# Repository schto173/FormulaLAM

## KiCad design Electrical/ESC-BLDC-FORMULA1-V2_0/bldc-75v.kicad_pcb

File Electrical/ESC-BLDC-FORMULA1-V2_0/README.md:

# ESC-BLDC-FORMULA1 V2.0 (work in progress – placement only, NOT routed, NOT orderable)

Redesign of the V1.2 ESC HAT (DRV8353RS + 6x CSD19532Q5B, SimpleFOC, NUCLEO-G474RE). V1.2 stays untouched in
`../ESC-BLDC-FORMULA1-V1_2/` (those are the files that were ordered).

## Background: how V1.2 board #1 failed
At ~45 V and ~93 % modulation the DRV8353 faulted and its internal low-side gate-drive supply was permanently
damaged (GDUV, VGLS 3 V instead of ~11 V). Not a component defect (C29 is not the cause); the root cause is not
determined yet – see `../ESC-BLDC-FORMULA1-V1_2/CLAUDE.md`. Trace length alone does not explain it: TI's
DRV8353RH-EVM has gate paths of the same length as V1.2. V2 follows that TI board (same parts, low-side shunts
into the DRV8353 amplifiers, DRV beside the FETs) and must survive a 60 V battery.

## What changed vs V1.2
- **Power supply (option A):** DRV8353 buck makes 12 V (VBUCK) for VM only, faster (R34 180k ≈ 480 kHz, L1 100 µH 6x6);
  TPS562201 makes 5 V from 12 V (replaces the LM5164 58 V buck). 5 V now comes up at ~6 V bus.
- **Phase voltage sensing removed** (U3 + dividers) – SimpleFOC does not use it. Fuse F1 removed (fuse goes in the battery cable).
- **Bus caps:** 3x THT 330 µF 100 V, 16x25 mm (C11, C21, C68; Samyoung NXA C346987 as on V1.2, 1.65 A ripple each
  = ~5 A, enough for 20 A bursts) + MLCCs in every half-bridge; TVS SMCJ60A (C224057; starts conducting at 66.7 V, so the board is safe with up to a 60 V battery).
- **Wheel speed input** J11 (JST-XH 3P: 1 = +5V, 2 = SIG, 3 = GND) → D10 / R78 4.7k to 3V3 / C73 → **PC6 (TIM3_CH1)**.
- **Test points:** TP1/TP2 Keystone 5001 GND loops for the scope clip (power side / logic side), pads TP3 VGLS,
  TP4 VCP, TP5 12 V, TP6 5 V, TP7 3.3 V.
- **Motor pads** are three single 2.5 mm² solder-wire pads: J6 = MOTC, J12 = MOTB, J13 = MOTA.
- Freed Nucleo pins: PB0, PC0, PC2 (were phase voltage sensing).

## Layout (board 110.5 x 90 mm, x 143–253.5 / y 44–134)
- Sits on top of the Nucleo (sockets on our bottom side); the **ST-LINK / USB end of the Nucleo stays uncovered**.
- **Power stage "pinwheel"** (after TI's DRV8353RS EVM): DRV rotated 45°, one half-bridge cell per DRV pin group –
  phase C above, B right, A below – so every phase gets a short gate/sense path (14–26 mm straight line; V1 had
  30–45 mm). Each cell: shunt (Kelvin, net tie under the body) → LS FET over HS FET → motor pad at the outer edge,
  MLCCs right beside the HS drain. Route GHx with SHx and GLx with SPx as tight pairs.
- Battery pads J5 + TVS at the top-right edge, bulk caps in the right corners; plan an inner VDRAIN plane under
  the power stage and a solid GND plane.
- Connectors next to the Nucleo pins they use: wheel / CAN / halls in the strip above CN10, UART / LEDs / throttle
  in the strip below CN7.
- M3 holes in the 4 corners; the Nucleo's own 3 holes are kept for standoffs.

## Before ordering
- Route the board; check that the HAT clears the Nucleo's Arduino headers (socket height).
- `tools/lcsc_map.py` is still the V1.2 map → update for V2 parts (U6, L3, C68–C73, R75–R78, D10, J11, J12, J13,
  TP1/TP2 = C238122; TP3–TP7 are bare pads) before running `gen_jlc.py`.
- Firmware: wheel input on PC6; 5 V rail now from VBUCK.

Placement is scripted: `tools/v2_place.py` (positions), `tools/v2_pcb_prepare.py` (netlist → board),
`tools/v2_sch_*.py` (schematic changes, each run once).

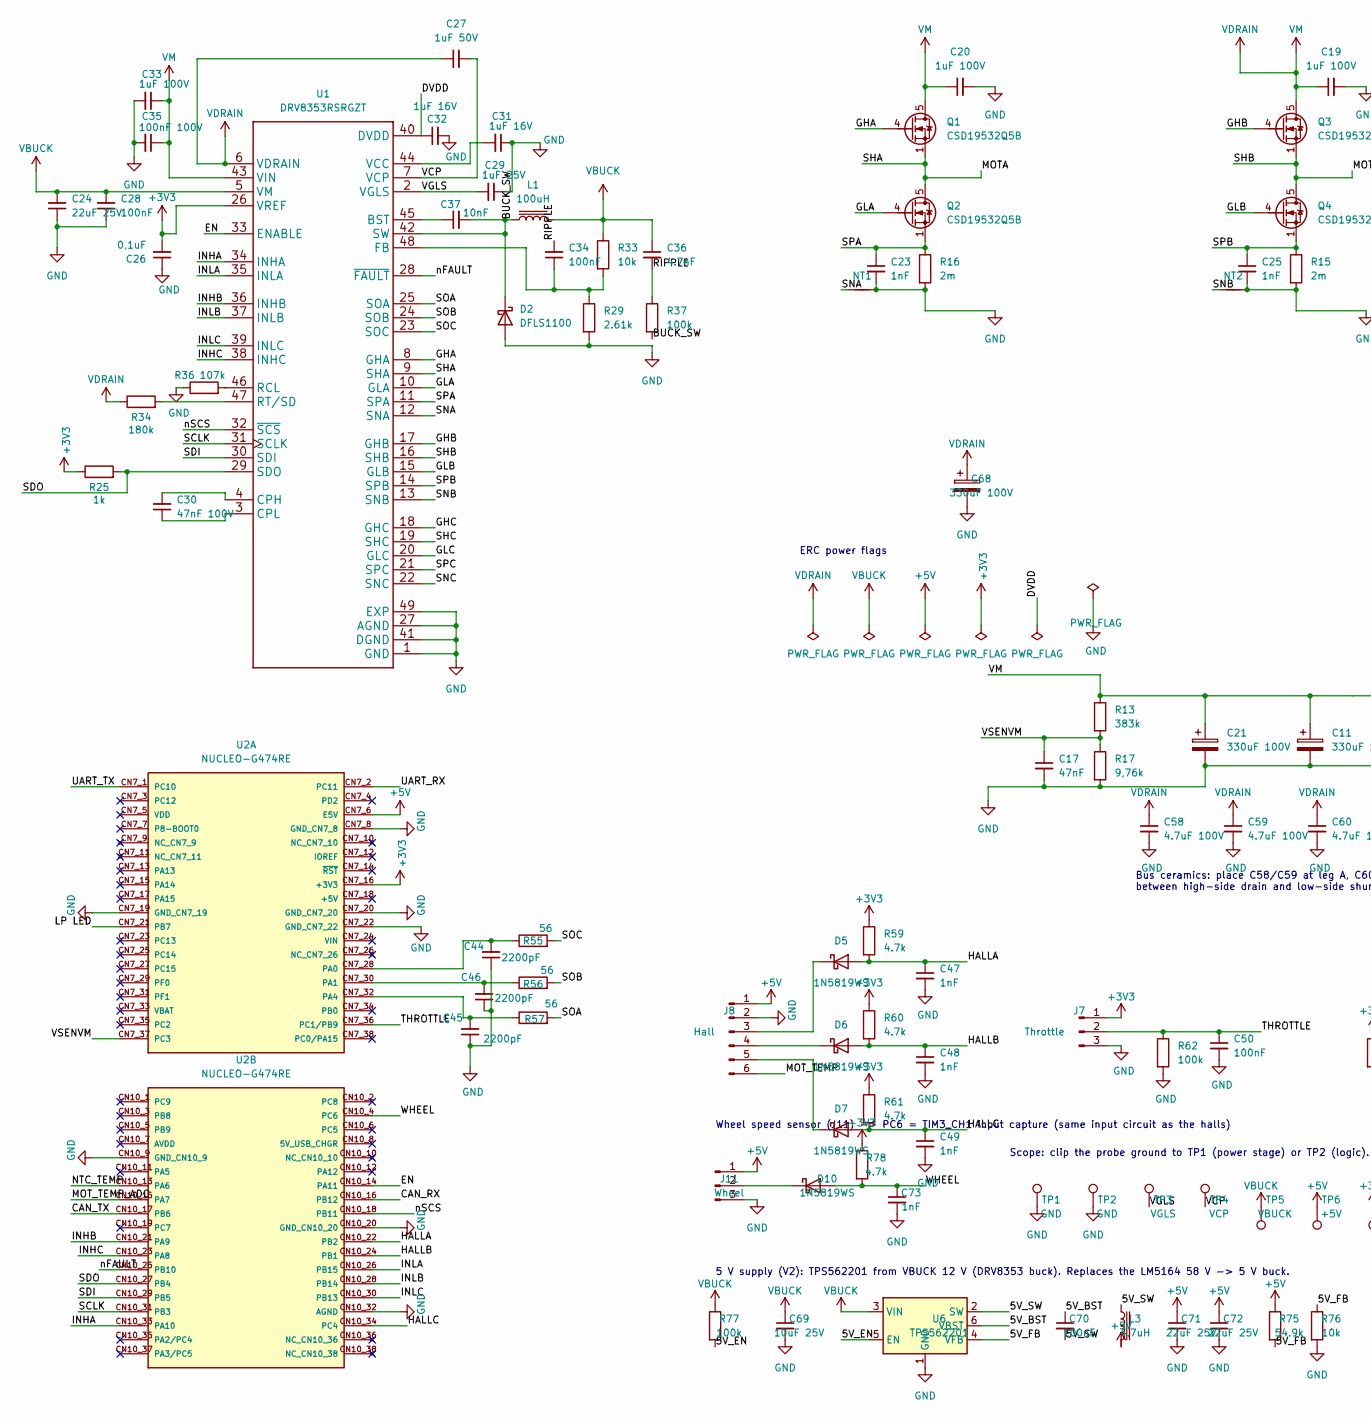
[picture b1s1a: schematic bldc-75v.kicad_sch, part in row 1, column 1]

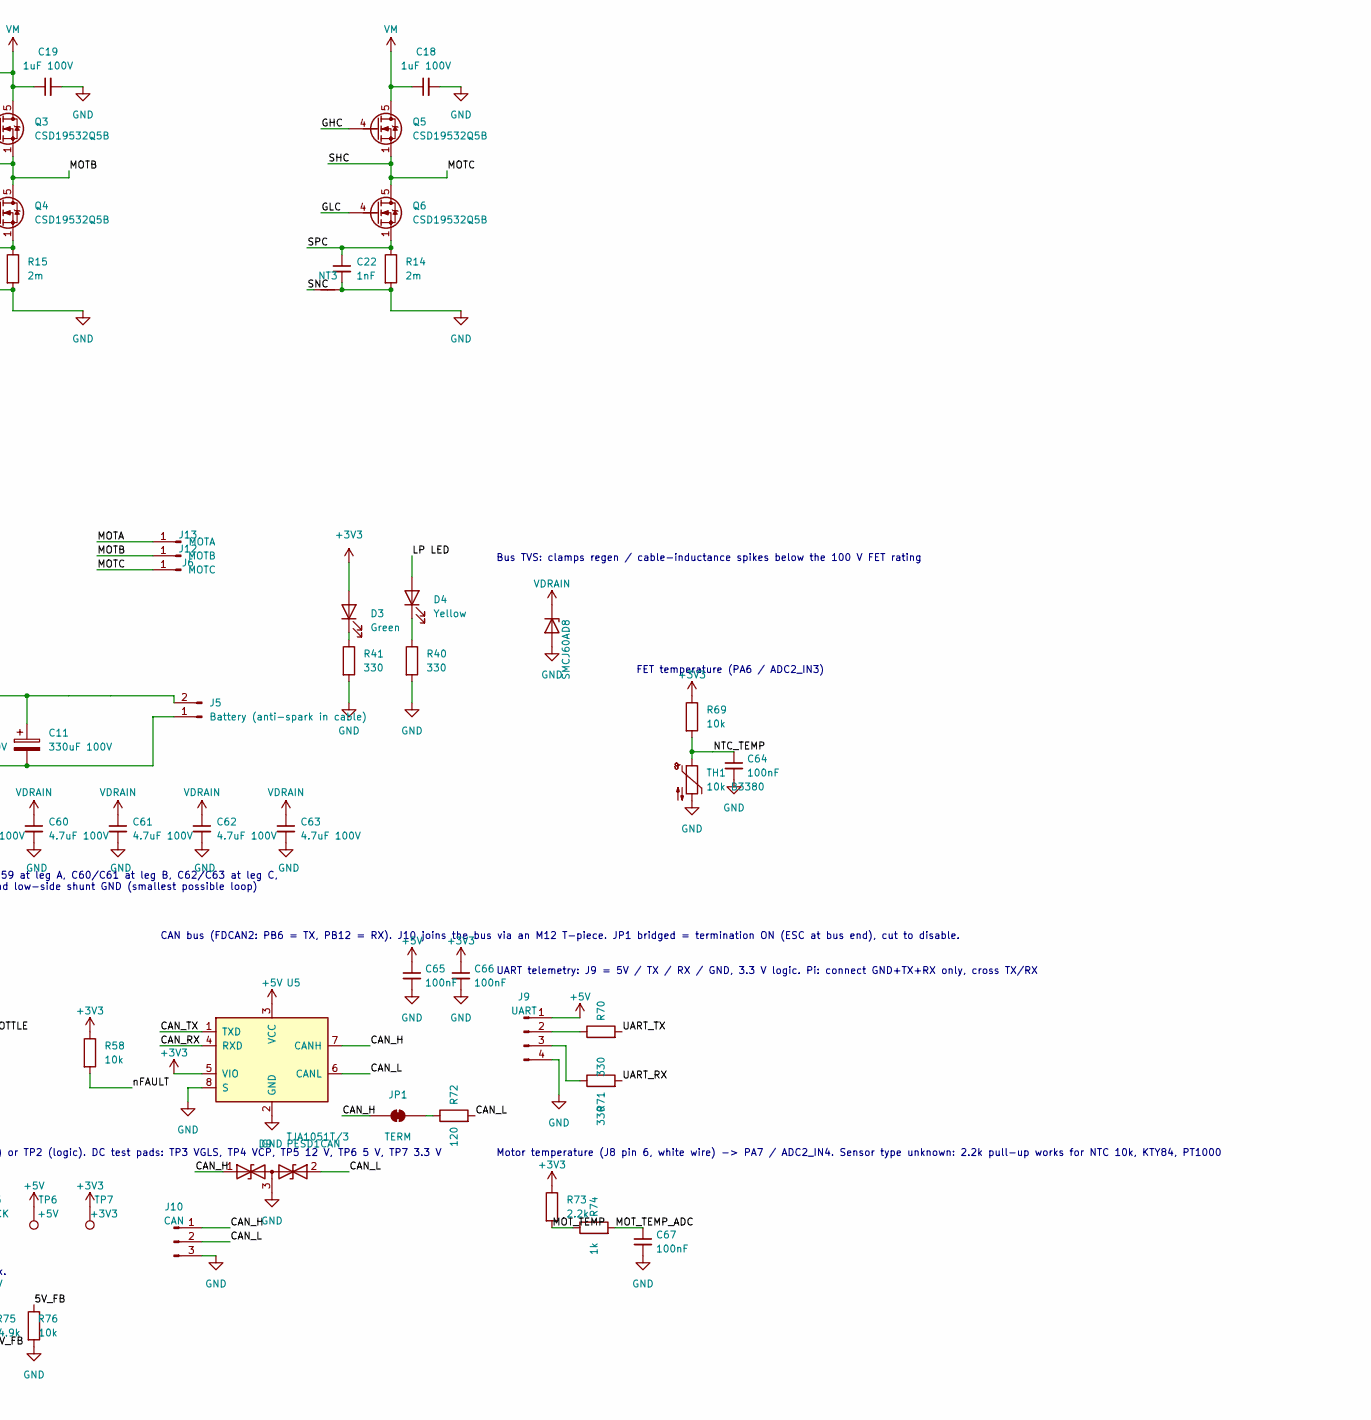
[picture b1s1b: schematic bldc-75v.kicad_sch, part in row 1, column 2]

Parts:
C11, C21, C68: 330uF 100V; CP_Radial_D16.0mm_P7.50mm; LCSC C346987
C17: 47nF; C_0603_1608Metric; LCSC C1622
C18, C19, C20, C33: 1uF 100V; C_1206_3216Metric; LCSC C13832
C22, C23, C25, C47, C48, C49, C73: 1nF; C_0603_1608Metric; LCSC C1588
C24: 22uF 25V; C_0805_2012Metric; LCSC C45783
C26: 0,1uF; C_0603_1608Metric; LCSC C14663
C27: 1uF 50V; C_0603_1608Metric; LCSC C15849
C28, C34, C50, C64, C65, C66, C67, C70: 100nF; C_0603_1608Metric; LCSC C14663
C29: 1uF 25V; C_0603_1608Metric; LCSC C15849
C30: 47nF 100V; C_0603_1608Metric; LCSC C576852
C31, C32: 1uF 16V; C_0603_1608Metric; LCSC C15849
C35: 100nF 100V; C_0805_2012Metric; LCSC C28233
C36: 4.7nF; C_0603_1608Metric; LCSC C53987
C37: 10nF; C_0603_1608Metric; LCSC C57112
C44, C45, C46: 2200pF; C_0603_1608Metric; LCSC C1604
C58, C59, C60, C61, C62, C63: 4.7uF 100V; C_1210_3225Metric; LCSC C385986
C69: 10uF 25V; C_0805_2012Metric; LCSC C15850
C71, C72: 22uF 25V; C_1206_3216Metric; LCSC C12891
D2: DFLS1100; D_PowerDI-123; LCSC C107674
D3: Green; LED_0603_1608Metric; LCSC C12624
D4: Yellow; LED_0603_1608Metric; LCSC C2287
D5, D6, D7, D10: 1N5819WS; D_SOD-323; LCSC C191023
D8: SMCJ60A; D_SMC; LCSC C224057
D9: PESD1CAN; SOT-23; LCSC C15771
J5: Battery (anti-spark in cable); SolderWire-2.5sqmm_1x02_P8.8mm_D2.4mm_OD4.4mm
J6: MOTC; SolderWire-2.5sqmm_1x01_D2.4mm_OD4.4mm
J7: Throttle; JST_XH_B3B-XH-A_1x03_P2.50mm_Vertical; LCSC C144394
J8: Hall; JST_XH_B6B-XH-A_1x06_P2.50mm_Vertical; LCSC C144397
J9: UART; JST_XH_B4B-XH-A_1x04_P2.50mm_Vertical; LCSC C144395
J10: CAN; JST_XH_B3B-XH-A_1x03_P2.50mm_Vertical; LCSC C144394
J11: Wheel; JST_XH_B3B-XH-A_1x03_P2.50mm_Vertical; LCSC C144394
J12: MOTB; SolderWire-2.5sqmm_1x01_D2.4mm_OD4.4mm
J13: MOTA; SolderWire-2.5sqmm_1x01_D2.4mm_OD4.4mm
JP1: TERM; SolderJumper-2_P1.3mm_Bridged_RoundedPad1.0x1.5mm
L1: 100uH; L_Sunlord_SWPA6045S; LCSC C60633
L3: 4.7uH; L_Sunlord_SWPA4030S; LCSC C57269
NT1, NT2, NT3: NetTie_2; NetTie-2_SMD_Pad0.5mm
Q1, Q2, Q3, Q4, Q5, Q6: CSD19532Q5B; TDSON-8-1; LCSC C473333
R13: 383k; R_1206_3216Metric; LCSC C247277
R14, R15, R16: 2m; R_2512_6332Metric; LCSC C154685
R17: 9,76k; R_0603_1608Metric; LCSC C23128
R25, R74: 1k; R_0603_1608Metric; LCSC C21190
R29: 2.61k; R_0603_1608Metric; LCSC C22942
R33, R58, R69, R76: 10k; R_0603_1608Metric; LCSC C25804
R34: 180k; R_1206_3216Metric; LCSC C17923
R36: 107k; R_0603_1608Metric; LCSC C14889
R37: 100k; R_1206_3216Metric; LCSC C17900
R40, R41, R70, R71: 330; R_0603_1608Metric; LCSC C23138
R55, R56, R57: 56; R_0603_1608Metric; LCSC C25196
R59, R60, R61, R78: 4.7k; R_0603_1608Metric; LCSC C23162
R62, R77: 100k; R_0603_1608Metric; LCSC C25803
R72: 120; R_0603_1608Metric; LCSC C22787
R73: 2.2k; R_0603_1608Metric; LCSC C4190
R75: 54.9k; R_0603_1608Metric; LCSC C23077
TH1: 10k B3380; R_0402_1005Metric; LCSC C77131
TP1, TP2: GND; TestPoint_Keystone_5000-5004_Miniature; LCSC C238122
TP3: VGLS; TestPoint_Pad_D1.5mm
TP4: VCP; TestPoint_Pad_D1.5mm
TP5: VBUCK; TestPoint_Pad_D1.5mm
TP6: +5V; TestPoint_Pad_D1.5mm
TP7: +3V3; TestPoint_Pad_D1.5mm
U1: DRV8353RSRGZT; QFN50P700X700X100-49N; PARTREV A; LCSC C506246
U2: NUCLEO-G474RE; Nucleo64_Morpho_HAT; PARTREV 17
U5: TJA1051T/3; SOIC-8_3.9x4.9mm_P1.27mm; LCSC C38695
U6: TPS562201; TSOT-23-6; LCSC C90061

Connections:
+3V3: C26.2, C66.1, D3.2 (A), J7.1, R25.1, R58.1, R59.1, R60.1, R61.1, R69.1, R73.1, R78.1, TP7.1, U1.26 (VREF), U2.CN7_16 (+3V3), U5.5 (VIO)
+5V: C65.1, C71.1, C72.1, J8.1, J9.1, J11.1, L3.2, R75.1, TP6.1, U2.CN7_6 (E5V), U5.3 (VCC)
/5V_BST: C70.1, U6.6 (VBST)
/5V_EN: R77.2, U6.5 (EN)
/5V_FB: R75.2, R76.1, U6.4 (VFB)
/5V_SW: C70.2, L3.1, U6.2 (SW)
/BUCK_SW: C37.2, D2.1 (K), L1.1, R37.2, U1.42 (SW)
/CAN_H: D9.1 (A1), J10.1, JP1.1 (A), U5.7 (CANH)
/CAN_L: D9.2 (A2), J10.2, R72.2, U5.6 (CANL)
/CAN_RX: U2.CN10_16 (PB12), U5.4 (RXD)
/CAN_TX: U2.CN10_17 (PB6), U5.1 (TXD)
/DVDD: C32.1, U1.40 (DVDD)
/EN: U1.33 (ENABLE), U2.CN10_14 (PA11)
/GHA: Q1.4 (G), U1.8 (GHA)
/GHB: Q3.4 (G), U1.17 (GHB)
/GHC: Q5.4 (G), U1.18 (GHC)
/GLA: Q2.4 (G), U1.10 (GLA)
/GLB: Q4.4 (G), U1.15 (GLB)
/GLC: Q6.4 (G), U1.20 (GLC)
/HALLA: C47.1, D5.2 (A), R59.2, U2.CN10_22 (PB2)
/HALLB: C48.1, D6.2 (A), R60.2, U2.CN10_24 (PB1)
/HALLC: C49.1, D7.2 (A), R61.2, U2.CN10_34 (PC4)
/INHA: U1.34 (INHA), U2.CN10_33 (PA10)
/INHB: U1.36 (INHB), U2.CN10_21 (PA9)
/INHC: U1.38 (INHC), U2.CN10_23 (PA8)
/INLA: U1.35 (INLA), U2.CN10_26 (PB15)
/INLB: U1.37 (INLB), U2.CN10_28 (PB14)
/INLC: U1.39 (INLC), U2.CN10_30 (PB13)
/LP LED: D4.2 (A), U2.CN7_21 (PB7)
/MOTA: J13.1, Q1.1 (S), Q1.2 (S), Q1.3 (S), Q2.5 (D), U1.9 (SHA)
/MOTB: J12.1, Q3.1 (S), Q3.2 (S), Q3.3 (S), Q4.5 (D), U1.16 (SHB)
/MOTC: J6.1, Q5.1 (S), Q5.2 (S), Q5.3 (S), Q6.5 (D), U1.19 (SHC)
/MOT_TEMP: J8.6, R73.2, R74.1
/MOT_TEMP_ADC: C67.1, R74.2, U2.CN10_15 (PA7)
/NTC_TEMP: C64.1, R69.2, TH1.1, U2.CN10_13 (PA6)
/RIPPLE: C34.2, C36.2, R37.1
/SCLK: U1.31 (SCLK), U2.CN10_31 (PB3)
/SDI: U1.30 (SDI), U2.CN10_29 (PB5)
/SDO: R25.2, U1.29 (SDO), U2.CN10_27 (PB4)
/SNA: NT1.1, U1.12 (SNA)
/SNB: NT2.1, U1.13 (SNB)
/SNC: NT3.1, U1.22 (SNC)
/SOA: R57.2, U1.25 (SOA)
/SOB: R56.2, U1.24 (SOB)
/SOC: R55.2, U1.23 (SOC)
/SPA: C23.1, Q2.1 (S), Q2.2 (S), Q2.3 (S), R16.1, U1.11 (SPA)
/SPB: C25.1, Q4.1 (S), Q4.2 (S), Q4.3 (S), R15.1, U1.14 (SPB)
/SPC: C22.1, Q6.1 (S), Q6.2 (S), Q6.3 (S), R14.1, U1.21 (SPC)
/THROTTLE: C50.1, J7.2, R62.1, U2.CN7_36 (PC1/PB9)
/UART_RX: R71.2, U2.CN7_2 (PC11)
/UART_TX: R70.2, U2.CN7_1 (PC10)
/VCP: C27.2, TP4.1, U1.7 (VCP)
/VGLS: C29.2, TP3.1, U1.2 (VGLS)
/VSENVM: C17.1, R13.2, R17.1, U2.CN7_37 (PC3)
/WHEEL: C73.1, D10.2 (A), R78.2, U2.CN10_4 (PC6)
/nFAULT: R58.2, U1.28 (~FAULT), U2.CN10_25 (PB10)
/nSCS: U1.32 (~SCS), U2.CN10_18 (PB11)
GND: C11.2, C17.2, C18.2, C19.2, C20.2, C21.2, C22.2, C23.2, C24.1, C25.2, C26.1, C28.1, C29.1, C31.1, C32.2, C33.2, C35.2, C44.1, C45.1, C46.1, C47.2, C48.2, C49.2, C50.2, C58.2, C59.2, C60.2, C61.2, C62.2, C63.2, C64.2, C65.2, C66.2, C67.2, C68.2, C69.2, C71.2, C72.2, C73.2, D2.2 (A), D8.2 (A), D9.3 (common), J5.1, J7.3, J8.2, J9.4, J10.3, J11.3, NT1.2, NT2.2, NT3.2, R14.2, R15.2, R16.2, R17.2, R29.2, R36.1, R40.2, R41.2, R62.2, R76.2, TH1.2, TP1.1, TP2.1, U1.1 (GND), U1.27 (AGND), U1.41 (DGND), U1.49 (EXP), U2.CN7_8 (GND_CN7_8), U2.CN7_19 (GND_CN7_19), U2.CN7_20 (GND_CN7_20), U2.CN7_22 (GND_CN7_22), U2.CN10_9 (GND_CN10_9), U2.CN10_20 (GND_CN10_20), U2.CN10_32 (AGND), U5.2 (GND), U5.8 (S), U6.1 (GND)
unnamed: D3.1 (K), R41.1
unnamed: D4.1 (K), R40.1
unnamed: D5.1 (K), J8.3
unnamed: D6.1 (K), J8.4
unnamed: D7.1 (K), J8.5
unnamed: D10.1 (K), J11.2
unnamed: J9.2, R70.1
unnamed: J9.3, R71.1
unnamed: JP1.2 (B), R72.1
unnamed: C37.1, U1.45 (BST)
unnamed: C30.2, U1.4 (CPH)
unnamed: C30.1, U1.3 (CPL)
unnamed: C34.1, R29.1, R33.2, U1.48 (FB)
unnamed: R36.2, U1.46 (RCL)
unnamed: R34.2, U1.47 (RT/SD)
unnamed: C31.2, U1.44 (VCC)
unnamed: C44.2, R55.1, U2.CN7_28 (PA0)
unnamed: C46.2, R56.1, U2.CN7_30 (PA1)
unnamed: C45.2, R57.1, U2.CN7_32 (PA4)
VBUCK: C24.2, C28.2, C36.1, C69.1, L1.2, R33.1, R77.1, TP5.1, U1.5 (VM), U6.3 (VIN)
VDRAIN: C11.1, C18.1, C19.1, C20.1, C21.1, C27.1, C33.1, C35.1, C58.1, C59.1, C60.1, C61.1, C62.1, C63.1, C68.1, D8.1 (K), J5.2, Q1.5 (D), Q3.5 (D), Q5.5 (D), R13.1, R34.1, U1.6 (VDRAIN), U1.43 (VIN)

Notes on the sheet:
Bus ceramics: place C58/C59 at leg A, C60/C61 at leg B, C62/C63 at leg C, between high-side drain and low-side shunt GND (smallest possible loop)
ERC power flags
Bus TVS: clamps regen / cable-inductance spikes below the 100 V FET rating
FET temperature (PA6 / ADC2_IN3)
UART telemetry: J9 = 5V / TX / RX / GND, 3.3 V logic. Pi: connect GND+TX+RX only, cross TX/RX
CAN bus (FDCAN2: PB6 = TX, PB12 = RX). J10 joins the bus via an M12 T-piece. JP1 bridged = termination ON (ESC at bus end), cut to disable.
Motor temperature (J8 pin 6, white wire) -> PA7 / ADC2_IN4. Sensor type unknown: 2.2k pull-up works for NTC 10k, KTY84, PT1000
5 V supply (V2): TPS562201 from VBUCK 12 V (DRV8353 buck). Replaces the LM5164 58 V -> 5 V buck.
Wheel speed sensor (J11) -> PC6 = TIM3_CH1 input capture (same input circuit as the halls)
Scope: clip the probe ground to TP1 (power stage) or TP2 (logic). DC test pads: TP3 VGLS, TP4 VCP, TP5 12 V, TP6 5 V, TP7 3.3 V

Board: 4 copper layers, 122 parts (0 on the bottom side), 79 nets, no tracks yet.

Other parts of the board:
H1, H2, H3, H4: M3; MountingHole_3.2mm_M3

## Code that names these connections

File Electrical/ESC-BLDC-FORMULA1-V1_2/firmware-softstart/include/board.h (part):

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// ---- throttle (J7: 1 = 3.3 V, 2 = signal, 3 = GND; 100k pull-down -> unplugged reads 0 V) - step 5 only --
// Throttle 0..100 % -> 0..limit A (limit = CURRENT_LIMIT, change live with "L"). Calibrate live: release fully
// + "AI", press fully + "AF"; then put the printed values here.
#define THROTTLE_ON_AT_START 1    // 1: throttle controls the current after start-up ("A0" = off, T commands again)
// hall throttle on 3.3 V (2026-10-14): ~0.87 V released, ~2.60 V fully pressed -> with dead band:
#define THROTTLE_IDLE_V   0.97f   // V at and below: 0 A
#define THROTTLE_FULL_V   2.55f   // V at and above: full current
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// while the motor is slower than the target; never negative (no braking - the freewheel hub can't pass it on).
// The current rises at most CURRENT_RAMP_A_S (soft freewheel engagement) and drops at once. Released = 0 A,
// the motor spins down, the car rolls; once the motor stands still the DRV goes to COAST (all FETs off).
#define GEAR_RATIO        9.41f   // motor turns per wheel turn (2026-10-29: pinion 15 -> 22 teeth, 13.8 x 15/22; was 8:1, 13.8:1)
#define WHEEL_DIAMETER_M  0.508f  // outer diameter with tyre (20" is often 0.48-0.50) <- CONFIRM
#define SPEED_MAX_KMH     40.0f   // throttle 100 %
#define MOTOR_DIRECTION   1       // +1 / -1: which way is forward (+1 = normal again with the new gearing 2026-10-26;
                                  //   was -1 with 8:1; live: "R1" normal, "R0" reversed, at standstill)
#define SPEED_P_A_PER_KMH 2.0f    // A per km/h too slow (5 km/h too slow = 10 A); P only -> holds ~0.5 km/h low
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// (almost) stopped -> for TAKEUP_MS the motor only creeps at TAKEUP_KMH with at most TAKEUP_AMPS (enough for the
// ~2 A cogging, too little to slam the clutch), whatever the pedal does; then the launch curve takes over.
#define TAKEUP_MS         1000    // ms
#define TAKEUP_BELOW_KMH  2.0f    // only when the motor is slower than this at the moment the throttle is pressed
#define TAKEUP_KMH        1.0f    // creep speed (motor, km/h equivalent; ~100 rpm at 9.41:1)
#define TAKEUP_AMPS       4.0f    // A max during take-up
#define TAKEUP_P_A_PER_KMH 4.0f   // creep controller: 4 A at standstill, 0 A at TAKEUP_KMH
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
// ---- gate driver (DRV8353RS) --------------------------------------------------------------------
// 6-PWM on TIM1 complementary pairs: phase A = CH3/CH3N, B = CH2/CH2N, C = CH1/CH1N
#define PIN_INHA   PA10
#define PIN_INLA   PB15
#define PIN_INHB   PA9
#define PIN_INLB   PB14
#define PIN_INHC   PA8
#define PIN_INLC   PB13
#define PIN_DRV_EN     PA11       // DRV8353 ENABLE (driven by us, not by SimpleFOC: going low resets its registers)
#define PIN_DRV_FAULT  PB10       // nFAULT, open drain, low = fault
#define PIN_DRV_SCK    PB3
#define PIN_DRV_MISO   PB4        // DRV SDO
#define PIN_DRV_MOSI   PB5        // DRV SDI
#define PIN_DRV_CS     PB11       // DRV nSCS

// ---- current sense: DRV8353 amplifiers on 2 mOhm shunts, all on ADC2 ------------------------------
#define PIN_SOA    PA4            // SOA -> R57 -> PA4 (CN7_32)  note: A and C are NOT in pin order
#define PIN_SOB    PA1            // SOB -> R56 -> PA1 (CN7_30)
#define PIN_SOC    PA0            // SOC -> R55 -> PA0 (CN7_28)
#define SHUNT_OHMS 0.002f
#define CSA_GAIN   10.0f          // must match the CSA_GAIN written in drv8353.h (10 since 2026-11-09, was 20)

// ---- sensors ------------------------------------------------------------------------------------
#define PIN_HALL_A PB2
#define PIN_HALL_B PB1
#define PIN_HALL_C PC4            // 4.7k pull-ups to 3.3 V on the board
#define PIN_VBUS   PC3            // divider 383k / 9.76k
#define PIN_NTC    PA6            // 10k pull-up to 3.3 V, NTC 10k B3380 to GND (next to Q4)       ADC2_IN3
#define PIN_MOT_TEMP PA7          // motor sensor: 2.2k pull-up to 3.3 V, 1k series, 100 nF         ADC2_IN4
#define PIN_THROTTLE PC1
#define PIN_LED    PB7

#define VBUS_DIVIDER ((383.0f + 9.76f) / 9.76f)
// Bus voltage, temperatures and throttle: read with ain::... from analog_in.h, never with analogRead().
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
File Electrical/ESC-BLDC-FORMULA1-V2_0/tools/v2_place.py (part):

"""V2 placement. Board = HAT over the MCU end of the NUCLEO-64 (ST-LINK/USB end left free) + power-stage extension on the
side away from the USB, + connector strips above CN10 and below CN7.  Outline x 143..241, y 44..134 (v2_pcb_prepare.py).
Nucleo pins: DRV logic / halls / CAN / wheel / temps on CN10 (top), UART / +5V / sense / throttle / VSENVM on CN7 (bottom).

Power stage = "pinwheel" around the DRV8353 (rotated 135 deg): one half-bridge cell per DRV pin group, each cell turned so
its gate entry faces those pins -> every phase gets the same short gate/sense path (phase B: gate corner, phase C: up-right
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ENTRY = {'B': (F(2, 2.0, 9.0), 0),         # phase B pins 13-17 at the gate corner -> cell to the right
         'C': (F(2, -0.75, 15.8), 90),     # phase C pins 18-22 on the up-right side -> cell above, mouth down
         'A': ((ax + 4.5, ay), 270)}       # phase A pins 8-12 on the down-right side -> cell below, mouth up
                                           # (3.5 mm right of the straight line: clears the VGLS/VCP caps of pins 1-7)
LS = {}
for ph, ((ex, ey), a) in ENTRY.items():
    mx, my = turn(MOUTH, a); lx, ly = ex - mx, ey - my; LS[ph] = (lx, ly)
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P('TH1', LS['B'][0] + 1.5, LS['B'][1] - 3.6, 0)          # FET temperature, above the phase-B low-side FET

# ---------------- DRV satellites --------------------------------------------------------------------------------------
# side 1 (pins 1-7 = GND VGLS CPL CPH VM VDRAIN VCP; 8-12 = phase A gate/sense -> keep t < -0.5 free)
R('C27', 1, 0.5, 6.3, inner=1)             # VDRAIN (pin 6 straight in) - VCP (pin 7 passes on the gate side)
R('C29', 1, 3.0, 6.3, inner=2)             # VGLS (board #1 failure) - nearest cap; GND pin 1 joins the pad 49
R('C28', 1, 0.6, 9.6, inner=2)             # VM (= VBUCK); VM/CPH/CPL leave between C27 and C29
R('C30', 1, 2.2, 9.6, inner=1)             # CPL-CPH flying cap
R('C33', 1, 5.0, 9.6, inner=1)            # VDRAIN 1 uF 100 V
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P('R69', 164.2, 66.8, 90); P('C64', 166.0, 66.8, 90)          # NTC_TEMP -> CN10_13
P('R73', 167.8, 66.8, 90); P('R74', 169.6, 66.8, 90); P('C67', 171.4, 66.8, 90)   # MOT_TEMP -> CN10_15
P('R58', 176.0, 66.8, 90); P('R25', 177.8, 66.8, 90)          # nFAULT / SDO pull-ups next to CN10_25 / _27
for i, ref in enumerate(('R55', 'C44', 'R56', 'C46', 'R57', 'C45')):   # current-sense RC right above PA0/PA1/PA4
    P(ref, 183.0 + 1.7 * i, 117.7, 90)
P('TP2', 175.0, 92.0, 0)                   # scope GND loop, logic side (middle of the Nucleo)

# ---------------- top strip (above CN10): signals that land on CN10 --------------------------------------------------
YJ = 47.4                                  # JST pin row
P('J11', 153.5, YJ, 0)                     # wheel sensor -> CN10_4 (PC6)
P('D10', 153.0, 54.0, 0); P('R78', 156.8, 54.0, 0); P('C73', 156.8, 56.2, 0)
P('J10', 165.0, YJ, 0)                     # CAN -> U5 -> CAN_RX CN10_16 / CAN_TX CN10_17 right below
P('U5', 167.5, 55.6, 180)                  # CANH/L pins left (toward J10), TXD/RXD right
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P('D4', 176.3, 129.0, 0); P('R40', 179.6, 129.0, 0)     # LP LED (CN7_21)
P('TP7', 183.0, 129.0, 0)                  # +3V3
P('R62', 185.2, YB, 90); P('C50', 186.9, YB, 90)        # throttle filter
P('J7', 191.0, YB, 0)                      # throttle -> CN7_36 (PC1)
P('R17', 200.0, 129.0, 90); P('C17', 201.7, 129.0, 90)  # VSENVM divider -> CN7_37

missing = sorted(set(fp) - placed - {'U2'})
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
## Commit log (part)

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2026-06-25 added new scripts from raspberry pi
2026-06-25 added new python scripts
2026-06-26 removed incoherent readme info
